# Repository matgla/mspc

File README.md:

# MSPC

Hardware for MSPC: a small modular computer built from a mainboard and extension cards that plug
into the MSPC bus. The mainboard runs [yasos](https://github.com/matgla/yasos.zig).

## Versions and branches

| branch | contents |
|---|---|
| `main` | the current hardware: the v2 boards (same as `mspc_v2`) |
| `mspc_v1` | the first generation, kept for reference |
| `mspc_v2` | the v2 boards as built |
| `mspc_v3` | the next revision (v3, not compatible with v2 cards), work in progress; `main` moves there when it is done and that point is tagged `mspcv3` |

## Repository layout

Every board is a KiCad project with its fabrication outputs next to it in `outputs/`.

| directory | board |
|---|---|
| `mainboard/` | Mainboard (project in `mainboard/mainboard/`). RP2350B (80-QFN), QSPI flash and PSRAM, microSD, HS8836A USB hub, TLV320DAC3203 audio DAC, 12 V input with BD9D321EFJ bucks, three MSPC bus sockets (2×10 and 2×15, 1.27 mm). 4 copper layers. |
| `gpu_vga_extension/` | VGA card: RP2350A (60-QFN), 2× W25Q32JV flash, AP2112K 3.3 V regulator, resistor-ladder RGB DAC and DB15 connector. 24 × 50 mm, 4 layers. |
| `gpu_dvi_card/` | DVI card: same core as the VGA card, with an HDMI-type receptacle carrying DVI. 24 × 50 mm, 4 layers. |
| `fpga_extension/` | FPGA card (project in `fpga_extension/fpga_extension/`): Lattice ECP5 LFE5UM-85F, W958D8NBYA HyperRAM, QSPI configuration flash, microSD, and an on-board RP2040 USB-C JTAG programmer. 47.5 × 50 mm, 6 layers. |
| `bus_adapter_20pin/` | Passive breakout from the 2×10 1.27 mm bus socket to two 1×10 2.54 mm headers. |
| `bus_adapter_30pin/` | Passive breakout from the 2×15 1.27 mm bus socket to two 1×15 2.54 mm headers. |
| `simulation/` | 2022 SPICE sandbox: KiCad/ngspice schematics (audio filter, power switch) and PySpice scripts. Not a board. |
| `libs/` | KiCad libraries shared by all boards (see below). |
| `docs/` | `mspc_v3_revision_plan.md` (v3 mainboard changes), `pcb_rules_jlcpcb.md` (mainboard stackup, JLCPCB order settings, fab export, design rules). |

## Working with the files

- The projects are in **KiCad 8** format. Newer KiCad versions upgrade them on the first save, and
  the result no longer opens in KiCad 8. Do such an upgrade as its own commit, with no design
  changes, so later diffs stay readable.
- Schematic PDFs (`outputs/schematic.pdf`) are tracked, so the schematics can be read without
  KiCad. Gerbers and drill files are not: plot them from the KiCad project when ordering a board.
  Per-machine files (backups, caches, `*.kicad_prl`, lock files, local history) are ignored too.

## Libraries

Every board uses the libraries in `libs/`. Each project's `sym-lib-table`, `fp-lib-table` and
`design-block-lib-table` point there through `${KIPRJMOD}`, so nothing has to be set up in KiCad.

| path | contents |
|---|---|
| `libs/symbols/` | symbol libraries, one per file; the nickname is the file name (`project_power`, `RP2040`, …) |
| `libs/footprints.pretty/` | footprints (nickname `footprints`) |
| `libs/RP2350_60QFN_minimal.pretty/`, `libs/RP2350_80QFN_minimal.pretty/` | RP2350 footprints and the small parts around them |
| `libs/3dmodels/` | STEP models; the footprints do not reference them yet |
| `libs/mspc.kicad_blocks/` | design blocks (KiCad 9+): circuits to reuse between boards, placed from the Design Blocks panel of the schematic editor. `TLV62569DRL_buck` is the FPGA card's 1.1 V buck. |

Add new parts to `libs/`, not to a project. A new symbol library file has to be added to the
`sym-lib-table` of every project.

## Known issues

- Some outputs are older than the boards they sit next to: the mainboard stencil (from v1), the
  GPU cards' schematic PDFs and stencils (from before the VGA/DVI split), and the FPGA card's
  schematic PDF. Regenerate them before the next order.
- The silkscreen of the 20-pin bus adapter reads "2x15" (copied from the 30-pin adapter).

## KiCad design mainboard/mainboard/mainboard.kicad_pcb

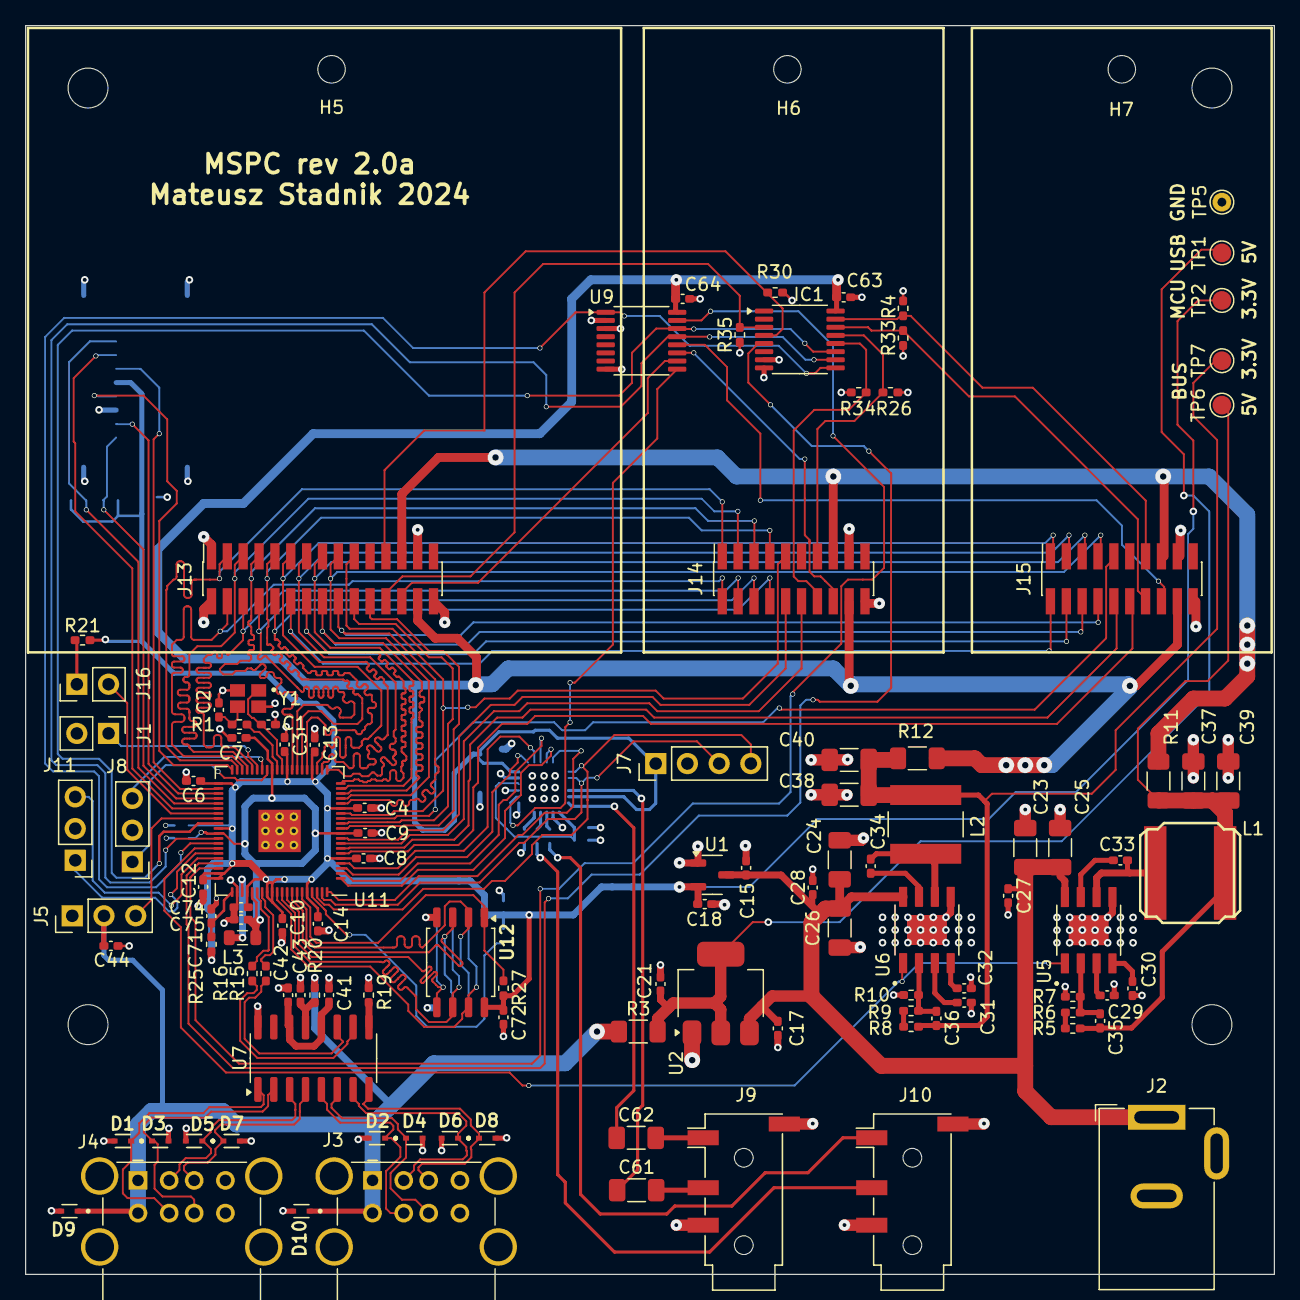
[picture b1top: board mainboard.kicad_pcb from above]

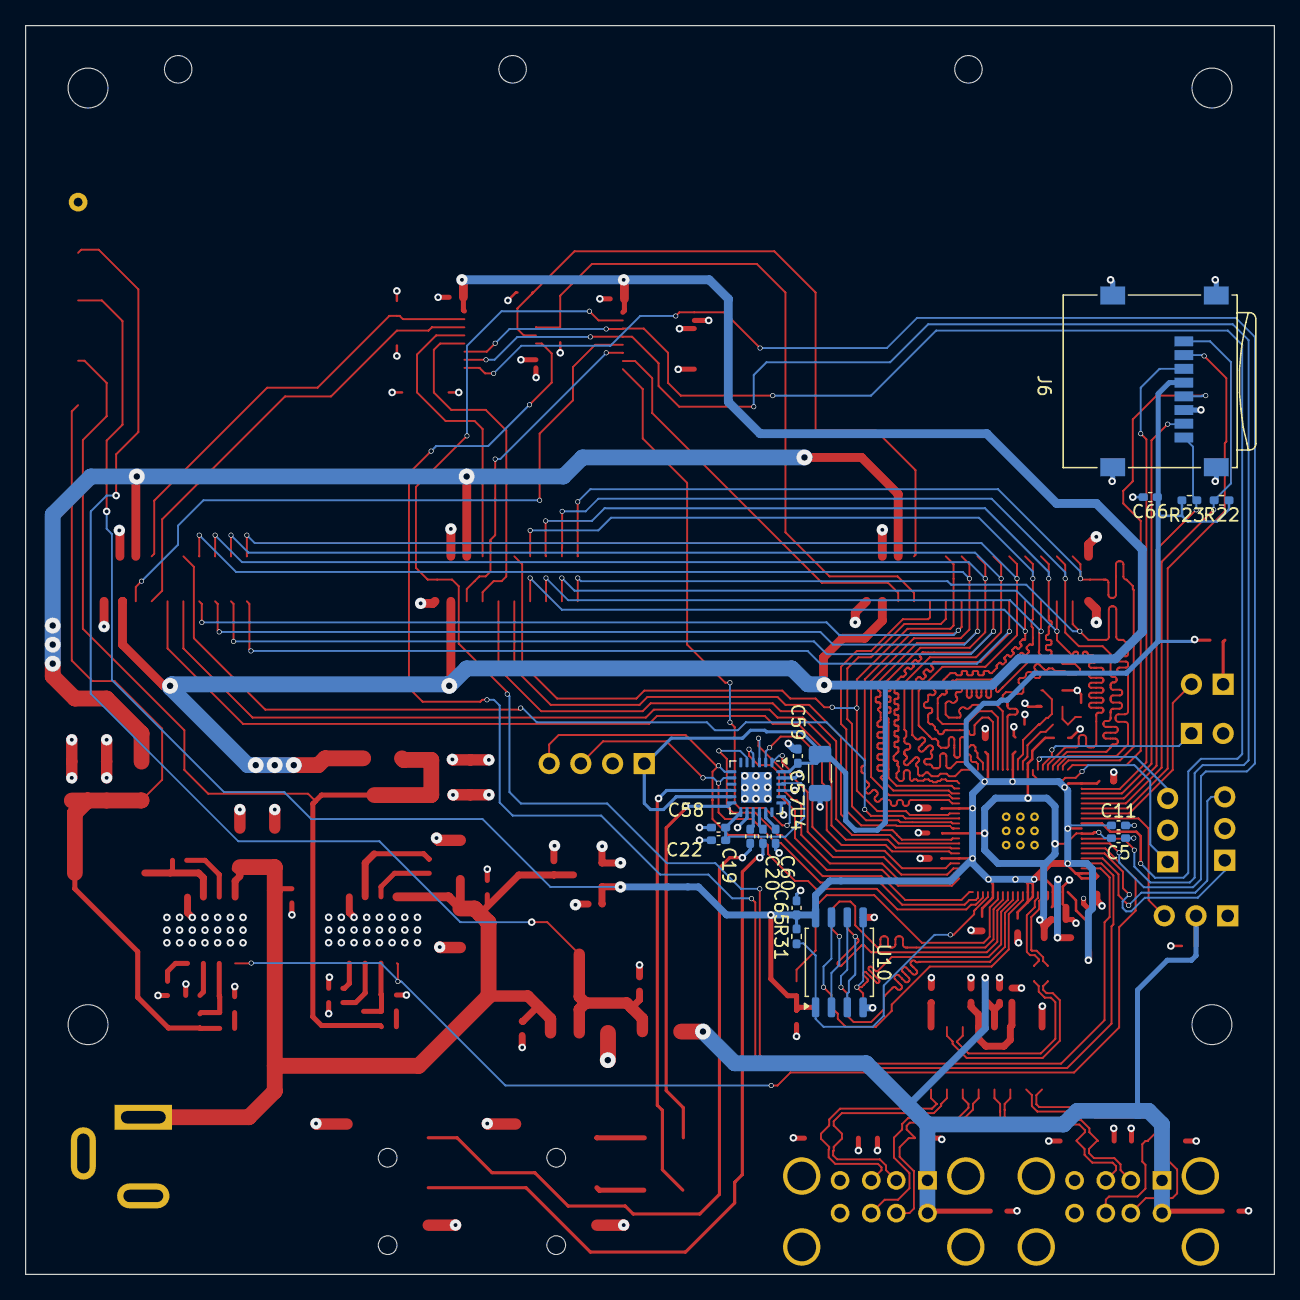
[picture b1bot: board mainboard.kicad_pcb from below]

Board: 4 copper layers, 100.0 x 100.0 mm, 135 parts (17 on the bottom side), 120 nets.

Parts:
C1, C2: 14p; C_0402_1005Metric_Pad0.74x0.62mm_HandSolder
C3, C4, C6, C7, C8, C9, C10, C11, C12, C13, C14, C19, C20, C27, C28, C33, C34, C42, C44, C58, C59, C63, C64, C65, C72: 100n; C_0402_1005Metric_Pad0.74x0.62mm_HandSolder
C5, C17, C41, C43, C71, C74, C75: 4.7u; C_0402_1005Metric_Pad0.74x0.62mm_HandSolder
C15, C22, C29, C31, C60: 1u; C_0402_1005Metric_Pad0.74x0.62mm_HandSolder
C18: 2.2u; C_0402_1005Metric_Pad0.74x0.62mm_HandSolder
C21: 10uF; C_0402_1005Metric_Pad0.74x0.62mm_HandSolder
C23, C24, C25, C26, C57: 10u; C_1206_3216Metric_Pad1.33x1.80mm_HandSolder
C30, C32: 3300p; C_0402_1005Metric_Pad0.74x0.62mm_HandSolder
C35, C36: 22p; C_0402_1005Metric_Pad0.74x0.62mm_HandSolder
C37, C38, C39, C40: 22u; C_1206_3216Metric_Pad1.33x1.80mm_HandSolder
C61, C62: 47u; C_1206_3216Metric_Pad1.33x1.80mm_HandSolder
C66: 10u; C_0402_1005Metric_Pad0.74x0.62mm_HandSolder
D1, D2, D3, D4, D5, D6, D7, D8, D9, D10: LESD5D5.0CT1G; TVS_LESD5D5.0CT1G
H1, H2, H3, H4: MountingHole; MountingHole_3.2mm_M3_DIN965
H5, H6, H7: MountingHole; MountingHole_2.2mm_M2_DIN965
IC1: SN74HCS151PWR; TSSOP-16_4.4x5mm_P0.65mm
J1, J16: Conn_01x02_Male; PinHeader_1x02_P2.54mm_Vertical
J2: Barrel_Jack_Switch; BarrelJack_GCT_DCJ200-10-A_Horizontal
J3, J4: USB_A_Wuerth_61400826021_Horizontal_Stacked
J5: Conn_01x03_Male; PinHeader_1x03_P2.54mm_Vertical
J6: Micro_SD_Card; microSD_HC_Wuerth_693072010801
J7: Conn_01x04_Female; PinHeader_1x04_P2.54mm_Vertical
J8, J11: Conn_01x03_Female; PinHeader_1x03_P2.54mm_Vertical
J9, J10: AudioJack4; Jack_3.5mm_PJ320D_Horizontal
J13: Connector A 16-bit; PinSocket_2x15_P1.27mm_Vertical_SMD
J14: Connector A 8-bit; PinSocket_2x10_P1.27mm_Vertical_SMD
J15: Connector B 8-bit; PinSocket_2x10_P1.27mm_Vertical_SMD
L1: 3.3u; NRS8030
L2: 2.2u; IND_NR6028T4R7M
L3: 3.3u; L_0805_2012Metric
R1, R21: 1k; R_0402_1005Metric_Pad0.72x0.64mm_HandSolder
R3, R11, R12: 0; R_1206_3216Metric_Pad1.30x1.75mm_HandSolder
R4, R22, R23, R26, R27, R30, R31, R33, R34, R35: 10k; R_0402_1005Metric_Pad0.72x0.64mm_HandSolder
R5: 120k; R_0402_1005Metric_Pad0.72x0.64mm_HandSolder
R6: 3.3k; R_0402_1005Metric_Pad0.72x0.64mm_HandSolder
R7, R10: 22k; R_0402_1005Metric_Pad0.72x0.64mm_HandSolder
R8: 68k; R_0402_1005Metric_Pad0.72x0.64mm_HandSolder
R9: 5.6k; R_0402_1005Metric_Pad0.72x0.64mm_HandSolder
R15, R16: 27.4R; R_0402_1005Metric_Pad0.72x0.64mm_HandSolder
R19: 100k; R_0402_1005Metric_Pad0.72x0.64mm_HandSolder
R20: 4.7; R_0402_1005Metric_Pad0.72x0.64mm_HandSolder
R25: 33; R_0402_1005Metric_Pad0.72x0.64mm_HandSolder
TP1, TP2, TP6, TP7: TestPoint; TestPoint_Pad_D1.5mm
TP5: TestPoint; TestPoint_THTPad_D1.5mm_Drill0.7mm
U1: AP2210; SOT-23-3
U2: LD1117S50TR_SOT223; SOT-223-3_TabPin2
U4: TLV320DAC3203IRGET; VQFN-24-1EP_4x4mm_P0.5mm_EP2.45x2.45mm
U5, U6: BD9D321EFJ; SOIC127P600X100-9N
U7: hs8836a; SOP-16_3.9x9.9mm_P1.27mm
U9: SN74LVC139APWR; TSSOP-16_4.4x5mm_P0.65mm
U10, U12: W25Q128JVS; SOIC-8_5.23x5.23mm_P1.27mm
U11: RP2350_80QFN; RP2350-QFN-80-1EP_10x10_P0.4mm_EP3.4x3.4mm_ThermalVias
Y1: ECS-120-8-36-CGN-TR; XTAL_ECS-120-8-36-CGN-TR

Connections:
+1V1_MCU: C5.1, C7.1, C9.1, C75.1, L3.1, U11.10 (DVDD), U11.32 (DVDD), U11.51 (DVDD), U11.65 (VREG_FB)
+3V3_BUS: C57.1, C59.1, C63.1, C64.1, IC1.16 (VCC), J7.1, J13.28, J14.18, J15.18, R12.1, U4.11 (LDOin), U4.24 (IOVDD), U9.16 (VCC)
+3V3_MCU: C3.1, C4.1, C6.1, C8.1, C10.1, C11.1, C12.1, C13.1, C14.1, C18.1, C65.1, C66.1, C72.1, C74.1, J6.4 (VDD), R21.2, R22.1, R23.1, R25.1, R27.2, R31.2, TP2.1, U1.2 (VOUT), U10.8 (VCC), U11.5 (IOVDD), U11.15 (IOVDD), U11.24 (IOVDD), U11.29 (IOVDD), U11.41 (IOVDD), U11.50 (IOVDD), U11.59 (ADC_AVDD), U11.60 (IOVDD), U11.64 (VREG_VIN), U11.68 (USB_OTP_VDD), U11.69 (QSPI_IOVDD), U11.76 (IOVDD), U12.8 (VCC)
+3V3_USB_HUB: C41.1, C42.1, U7.12 (DCP), U7.14 (V33)
+5V_BUS: J13.25, J14.15, J15.15, R11.1
+5V_VBUS: C44.1, D9.1, D10.1, J3.1 (VBUS1), J3.5 (VBUS2), J4.1 (VBUS1), J4.5 (VBUS2), J5.2, R3.1, R20.2
/RP2350 Core/Audio DAC/AUDIO.BCLK: U4.2 (BCLK), U11.4 (GPIO7)
/RP2350 Core/Audio DAC/AUDIO.DIN: U4.4 (DIN/MFP1), U11.1 (GPIO4)
/RP2350 Core/Audio DAC/AUDIO.DOUT: U4.5 (DOUT/MFP2), U11.80 (GPIO3)
/RP2350 Core/Audio DAC/AUDIO.MCLK: U4.1 (MCLK), U11.3 (GPIO6)
/RP2350 Core/Audio DAC/AUDIO.RESET#: U4.20 (RESET#), U9.9 (2Y3)
/RP2350 Core/Audio DAC/AUDIO.WCLK: U4.3 (WCLK), U11.2 (GPIO5)
/RP2350 Core/Audio DAC/AUDIO_OUT.L: C62.2, J9.T
/RP2350 Core/Audio DAC/AUDIO_OUT.R: C61.2, J9.R1
/RP2350 Core/Audio DAC/AUX_IN.L: C19.1, J10.T
/RP2350 Core/Audio DAC/AUX_IN.R: C20.1, J10.R1
/RP2350 Core/Audio DAC/I2C.SCL: J7.4, U4.7 (SCL/SS#), U11.78 (GPIO1)
/RP2350 Core/Audio DAC/I2C.SDA: J7.3, U4.8 (SDA/MOSI), U11.79 (GPIO2)
/RP2350 Core/BUS_DET_OUT: IC1.5 (Y), U11.57 (GPIO46_ADC6)
/RP2350 Core/BUS_RE#.IN: U9.15 (2G#), U11.58 (GPIO47_ADC7)
/RP2350 Core/MCU Connectors/BUS_CS#A0: J13.22, U11.11 (GPIO12)
/RP2350 Core/MCU Connectors/BUS_CS#A1: J13.20, U11.12 (GPIO13)
/RP2350 Core/MCU Connectors/BUS_CS#A2: J14.12, U11.8 (GPIO10)
/RP2350 Core/MCU Connectors/BUS_CS#A3: J14.10, U11.9 (GPIO11)
/RP2350 Core/MCU Connectors/BUS_CS#B0: J15.12, U11.6 (GPIO8)
/RP2350 Core/MCU Connectors/BUS_CS#B1: J15.10, U11.7 (GPIO9)
/RP2350 Core/MCU Connectors/BUS_DET.IN0: IC1.3 (D1), J13.24, R35.2
/RP2350 Core/MCU Connectors/BUS_DET.IN1: IC1.12 (D7), J14.14, R34.2
/RP2350 Core/MCU Connectors/BUS_DET.IN2: IC1.14 (D5), J15.14, R33.2
/RP2350 Core/MCU Connectors/BUS_INT.IN0: IC1.4 (D0), J13.23, R30.2
/RP2350 Core/MCU Connectors/BUS_INT.IN1: IC1.13 (D6), J14.13, R26.2
/RP2350 Core/MCU Connectors/BUS_INT.IN2: IC1.15 (D4), J15.13, R4.2
/RP2350 Core/MCU Connectors/BUS_NORTH.CLK0: J15.9, U11.13 (GPIO14)
/RP2350 Core/MCU Connectors/BUS_NORTH.CLK1: J13.19, J14.9, U11.14 (GPIO15)
/RP2350 Core/MCU Connectors/BUS_NORTH.D0: J13.18, J15.8, U11.16 (GPIO16)
/RP2350 Core/MCU Connectors/BUS_NORTH.D1: J13.17, J15.7, U11.17 (GPIO17)
/RP2350 Core/MCU Connectors/BUS_NORTH.D2: J13.16, J15.6, U11.18 (GPIO18)
/RP2350 Core/MCU Connectors/BUS_NORTH.D3: J13.15, J15.5, U11.19 (GPIO19)
/RP2350 Core/MCU Connectors/BUS_NORTH.D4: J13.14, J15.4, U11.20 (GPIO20)
/RP2350 Core/MCU Connectors/BUS_NORTH.D5: J13.13, J15.3, U11.21 (GPIO21)
/RP2350 Core/MCU Connectors/BUS_NORTH.D6: J13.12, J15.2, U11.22 (GPIO22)
/RP2350 Core/MCU Connectors/BUS_NORTH.D7: J13.11, J15.1, U11.23 (GPIO23)
/RP2350 Core/MCU Connectors/BUS_NORTH.D8: J13.10, J14.8, U11.25 (GPIO24)
/RP2350 Core/MCU Connectors/BUS_NORTH.D9: J13.9, J14.7, U11.26 (GPIO25)
/RP2350 Core/MCU Connectors/BUS_NORTH.D10: J13.8, J14.6, U11.27 (GPIO26)
/RP2350 Core/MCU Connectors/BUS_NORTH.D11: J13.7, J14.5, U11.28 (GPIO27)
/RP2350 Core/MCU Connectors/BUS_NORTH.D12: J13.6, J14.4, U11.36 (GPIO28)
/RP2350 Core/MCU Connectors/BUS_NORTH.D13: J13.5, J14.3, U11.37 (GPIO29)
/RP2350 Core/MCU Connectors/BUS_NORTH.D14: J13.4, J14.2, U11.38 (GPIO30)
/RP2350 Core/MCU Connectors/BUS_NORTH.D15: J13.3, J14.1, U11.39 (GPIO31)
/RP2350 Core/MCU Connectors/BUS_RE#.OUT0: J13.26, U9.10 (2Y2)
/RP2350 Core/MCU Connectors/BUS_RE#.OUT1: J14.16, U9.11 (2Y1)
/RP2350 Core/MCU Connectors/BUS_RE#.OUT2: J15.16, U9.12 (2Y0)
/RP2350 Core/MCU Connectors/DEBUG.SWCLK: J8.1, U11.33 (SWCLK)
/RP2350 Core/MCU Connectors/DEBUG.SWD: J8.3, U11.34 (SWD)
/RP2350 Core/MCU Connectors/UART.RX: J11.3, U11.56 (GPIO45_ADC5)
/RP2350 Core/MCU Connectors/UART.TX: J11.1, U11.55 (GPIO44_ADC4)
/RP2350 Core/MCU flash/QSPI.CSN0: R27.1, U11.75 (QSPI_SS), U12.1 (~CS)
/RP2350 Core/MCU flash/QSPI.CSN1: R31.1, U10.1 (~CS), U11.77 (GPIO0)
/RP2350 Core/MCU flash/QSPI.SCLK: U10.6 (CLK), U11.71 (QSPI_SCLK), U12.6 (CLK)
/RP2350 Core/MCU flash/QSPI.SD0: U10.5 (DI(IO0)), U11.72 (QSPI_SD0), U12.5 (DI(IO0))
/RP2350 Core/MCU flash/QSPI.SD1: U10.2 (DO(IO1)), U11.74 (QSPI_SD1), U12.2 (DO(IO1))
/RP2350 Core/MCU flash/QSPI.SD2: U10.3 (IO2), U11.73 (QSPI_SD2), U12.3 (IO2)
/RP2350 Core/MCU flash/QSPI.SD3: U10.7 (IO3), U11.70 (QSPI_SD3), U12.7 (IO3)
/RP2350 Core/MCU_RESET#: J1.1, U11.35 (RUN)
/RP2350 Core/Main bus control/BUS.CONTROL0: IC1.11 (A), U9.14 (2A), U11.49 (GPIO40_ADC0)
/RP2350 Core/Main bus control/BUS.CONTROL1: IC1.10 (B), U9.13 (2B), U11.52 (GPIO41_ADC1)
/RP2350 Core/Main bus control/BUS.CONTROL2: IC1.9 (C), U9.1 (1G#), U11.53 (GPIO42_ADC2)
/RP2350 Core/OSC_IN: C1.1, U11.30 (XIN), Y1.1 (IN/OUT)
/RP2350 Core/OSC_OUT: R1.2, U11.31 (XOUT)
/RP2350 Core/POWER_BUTTON: J16.2, U11.47 (GPIO38)
/RP2350 Core/POWER_LED_DATA: J5.3, U11.48 (GPIO39)
/RP2350 Core/SD Card/SDIO.CLK: J6.5 (CLK), U11.40 (GPIO32)
/RP2350 Core/SD Card/SDIO.CMD: J6.3 (CMD), U11.42 (GPIO33)
/RP2350 Core/SD Card/SDIO.D0: J6.7 (DAT0), U11.43 (GPIO34)
/RP2350 Core/SD Card/SDIO.D1: J6.8 (DAT1), R23.2, U11.44 (GPIO35)
/RP2350 Core/SD Card/SDIO.D2: J6.1 (DAT2), R22.2, U11.45 (GPIO36)
/RP2350 Core/SD Card/SDIO.D3: J6.2 (DAT3/CD), U11.46 (GPIO37)
/RP2350 Core/USB Hub/D1+: D8.1, J3.3 (D1+), U7.8 (DP1)
/RP2350 Core/USB Hub/D1-: D6.1, J3.2 (D1-), U7.7 (DM1)
/RP2350 Core/USB Hub/D2+: D4.1, J3.7 (D2+), U7.6 (DP2)
/RP2350 Core/USB Hub/D2-: D2.1, J3.6 (D2-), U7.5 (DM2)
/RP2350 Core/USB Hub/D3+: D7.1, J4.3 (D1+), U7.4 (DP3)
/RP2350 Core/USB Hub/D3-: D5.1, J4.2 (D1-), U7.3 (DM3)
/RP2350 Core/USB Hub/D4+: D3.1, J4.7 (D2+), U7.2 (DP4)
/RP2350 Core/USB Hub/D4-: D1.1, J4.6 (D2-), U7.1 (DM4)
/RP2350 Core/USB Hub/USB.D+: R16.2, U7.10 (DM)
/RP2350 Core/USB Hub/USB.D-: R15.2, U7.11 (DP)
/RP2350 Core/USB_D+: R16.1, U11.66 (USB_DM)
/RP2350 Core/USB_D-: R15.1, U11.67 (USB_DP)
/RP2350 Core/VREG_AVDD: C71.1, R25.2, U11.61 (VREG_AVDD)
/RP2350 Core/VREG_LX: L3.2, U11.63 (VREG_LX)
/power_supply/POWER_ENABLE: U5.1 (EN), U6.1 (EN), U11.54 (GPIO43_ADC3)
GND: C1.2, C2.2, C3.2, C4.2, C5.2, C6.2, C7.2, C8.2, C9.2, C10.2, C11.2, C12.2, C13.2, C14.2, C15.2, C17.2, C18.2, C21.2, C22.2, C23.2, C24.2, C25.2, C26.2, C27.2, C28.2, C29.2, C30.2, C31.2, C32.2, C37.2, C38.2, C39.2, C40.2, C41.2, C42.2, C43.2, C44.2, C57.2, C58.2, C59.2, C60.2, C63.2, C64.2, C65.2, C66.2, C71.2, C72.2, C74.2, C75.2, D1.2, D2.2, D3.2, D4.2, D5.2, D6.2, D7.2, D8.2, D9.2, D10.2, IC1.7 (~G), IC1.8 (GND), J1.2, J2.2, J3.4 (GND1), J3.8 (GND2), J3.9 (Shield), J4.4 (GND1), J4.8 (GND2), J4.9 (Shield), J5.1, J6.6 (VSS), J6.9 (SHIELD), J7.2, J8.2, J9.R2, J9.S, J10.R2, J10.S, J11.2, J13.1, J13.2, J13.27, J13.30, J14.17, J14.20, J15.17, J15.20, R4.1, R7.2, R10.2, R19.1, R26.1, R30.1, R33.1, R34.1, R35.1, TP5.1, U1.1 (GND), U2.1 (GND), U4.14 (AVSS), U4.19 (SPI_SELECT), U4.21 (DVSS), U4.23 (IOVSS), U5.5 (GND), U5.9 (FIN), U6.5 (GND), U6.9 (FIN), U7.16 (GND), U9.2 (1A), U9.3 (1B), U9.8 (GND), U10.4 (GND), U11.62 (VREG_PGND), U11.81 (GND), U12.4 (GND), Y1.2 (GND), Y1.4 (GND)
unnamed: C35.1, C37.1, C39.1, L1.2, R5.1, R11.2, TP6.1
unnamed: C36.1, C38.1, C40.1, L2.2, R8.1, R12.2, TP7.1
unnamed: J16.1, R21.1
unnamed: R5.2, R6.1
unnamed: R8.2, R9.1
unnamed: C21.1, R3.2, TP1.1, U2.2 (VO)
unnamed: C22.1, C58.1, U4.13 (AVDD), U4.22 (DVDD)
unnamed: C62.1, U4.12 (HPL)
unnamed: C61.1, U4.10 (HPR)
unnamed: C19.2, U4.15 (INL)
unnamed: C20.2, U4.16 (INR)
unnamed: C60.1, U4.17 (REF)
unnamed: C33.1, U5.7 (BOOT)
unnamed: C35.2, R6.2, R7.1, U5.2 (FB)
unnamed: C30.1, U5.4 (SS)
unnamed: C33.2, L1.1, U5.6 (SW)
unnamed: C29.1, U5.3 (VREG)
unnamed: C34.1, U6.7 (BOOT)
unnamed: C36.2, R9.2, R10.1, U6.2 (FB)
unnamed: C32.1, U6.4 (SS)
unnamed: C34.2, L2.1, U6.6 (SW)
unnamed: C31.1, U6.3 (VREG)
unnamed: R19.2, U7.9 (REF)
unnamed: C43.1, R20.1, U7.13 (VCC)
unnamed: C2.1, R1.1, Y1.3 (OUT/IN)
VDC: C15.1, C17.1, C23.1, C24.1, C25.1, C26.1, C27.1, C28.1, J2.1, U1.3 (VIN), U2.3 (VI), U5.8 (VIN), U6.8 (VIN)

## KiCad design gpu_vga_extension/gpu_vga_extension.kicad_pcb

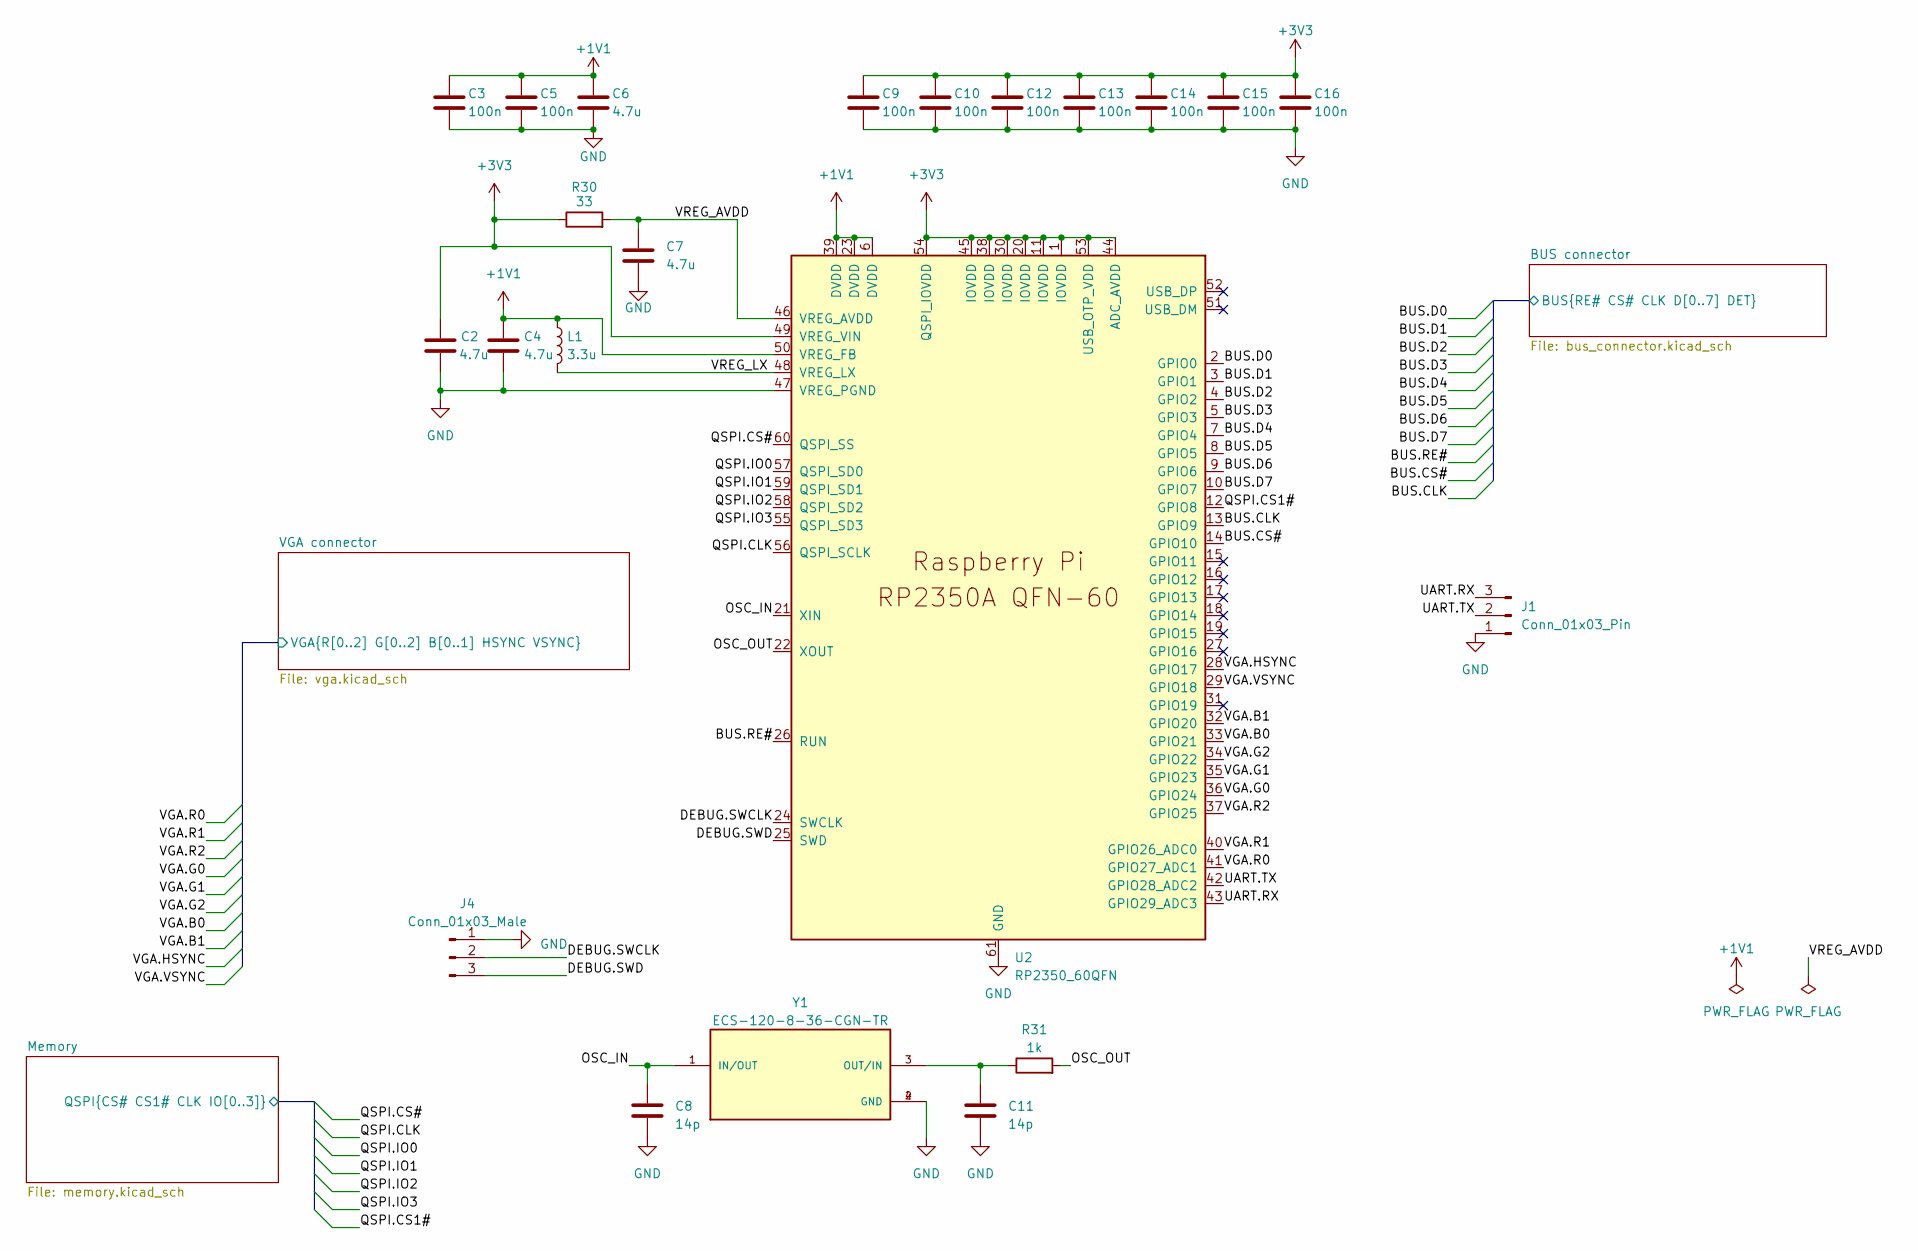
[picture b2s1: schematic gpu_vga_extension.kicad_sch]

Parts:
C2, C4, C6, C7: 4.7u; C_0402_1005Metric_Pad0.74x0.62mm_HandSolder
C3, C5, C9, C10, C12, C13, C14, C15, C16: 100n; C_0402_1005Metric_Pad0.74x0.62mm_HandSolder
C8, C11: 14p; C_0402_1005Metric_Pad0.74x0.62mm_HandSolder
J1: Conn_01x03_Pin; PinHeader_1x03_P2.54mm_Vertical
J4: Conn_01x03_Male; PinHeader_1x03_P2.54mm_Vertical
L1: 3.3u; L_0805_2012Metric_Pad1.15x1.40mm_HandSolder
R30: 33; R_0402_1005Metric_Pad0.72x0.64mm_HandSolder
R31: 1k; R_0402_1005Metric_Pad0.72x0.64mm_HandSolder
U2: RP2350_60QFN; RP2350-QFN-60-1EP_7x7_P0.4mm_EP3.4x3.4mm_ThermalVias
Y1: ECS-120-8-36-CGN-TR; XTAL_ECS-120-8-36-CGN-TR; PARTREV 2017

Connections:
+1V1: C3.1, C4.1, C5.1, C6.1, L1.1, U2.6 (DVDD), U2.23 (DVDD), U2.39 (DVDD), U2.50 (VREG_FB)
+3V3: C2.1, C9.1, C10.1, C12.1, C13.1, C14.1, C15.1, C16.1, R30.1, U2.1 (IOVDD), U2.11 (IOVDD), U2.20 (IOVDD), U2.30 (IOVDD), U2.38 (IOVDD), U2.44 (ADC_AVDD), U2.45 (IOVDD), U2.49 (VREG_VIN), U2.53 (USB_OTP_VDD), U2.54 (QSPI_IOVDD); also elsewhere on the board
/BUS connector/BUS.CLK: U2.13 (GPIO9); also elsewhere on the board
/BUS connector/BUS.CS#: U2.14 (GPIO10); also elsewhere on the board
/BUS connector/BUS.D0: U2.2 (GPIO0); also elsewhere on the board
/BUS connector/BUS.D1: U2.3 (GPIO1); also elsewhere on the board
/BUS connector/BUS.D2: U2.4 (GPIO2); also elsewhere on the board
/BUS connector/BUS.D3: U2.5 (GPIO3); also elsewhere on the board
/BUS connector/BUS.D4: U2.7 (GPIO4); also elsewhere on the board
/BUS connector/BUS.D5: U2.8 (GPIO5); also elsewhere on the board
/BUS connector/BUS.D6: U2.9 (GPIO6); also elsewhere on the board
/BUS connector/BUS.D7: U2.10 (GPIO7); also elsewhere on the board
/BUS connector/BUS.RE#: U2.26 (RUN); also elsewhere on the board
/DEBUG.SWCLK: J4.2, U2.24 (SWCLK)
/DEBUG.SWD: J4.3, U2.25 (SWD)
/Memory/QSPI.CLK: U2.56 (QSPI_SCLK); also elsewhere on the board
/Memory/QSPI.CS1#: U2.12 (GPIO8); also elsewhere on the board
/Memory/QSPI.CS#: U2.60 (QSPI_SS); also elsewhere on the board
/Memory/QSPI.IO0: U2.57 (QSPI_SD0); also elsewhere on the board
/Memory/QSPI.IO1: U2.59 (QSPI_SD1); also elsewhere on the board
/Memory/QSPI.IO2: U2.58 (QSPI_SD2); also elsewhere on the board
/Memory/QSPI.IO3: U2.55 (QSPI_SD3); also elsewhere on the board
/OSC_IN: C8.1, U2.21 (XIN), Y1.1 (IN/OUT)
/OSC_OUT: R31.2, U2.22 (XOUT)
/UART.RX: J1.3, U2.43 (GPIO29_ADC3)
/UART.TX: J1.2, U2.42 (GPIO28_ADC2)
/VGA connector/VGA.B0: U2.33 (GPIO21); also elsewhere on the board
/VGA connector/VGA.B1: U2.32 (GPIO20); also elsewhere on the board
/VGA connector/VGA.G0: U2.36 (GPIO24); also elsewhere on the board
/VGA connector/VGA.G1: U2.35 (GPIO23); also elsewhere on the board
/VGA connector/VGA.G2: U2.34 (GPIO22); also elsewhere on the board
/VGA connector/VGA.HSYNC: U2.28 (GPIO17); also elsewhere on the board
/VGA connector/VGA.R0: U2.41 (GPIO27_ADC1); also elsewhere on the board
/VGA connector/VGA.R1: U2.40 (GPIO26_ADC0); also elsewhere on the board
/VGA connector/VGA.R2: U2.37 (GPIO25); also elsewhere on the board
/VGA connector/VGA.VSYNC: U2.29 (GPIO18); also elsewhere on the board
/VREG_AVDD: C7.1, R30.2, U2.46 (VREG_AVDD)
/VREG_LX: L1.2, U2.48 (VREG_LX)
GND: C2.2, C3.2, C4.2, C5.2, C6.2, C7.2, C8.2, C9.2, C10.2, C11.2, C12.2, C13.2, C14.2, C15.2, C16.2, J1.1, J4.1, U2.47 (VREG_PGND), U2.61 (GND), Y1.2 (GND), Y1.4 (GND); also elsewhere on the board
unnamed: C11.1, R31.1, Y1.3 (OUT/IN)

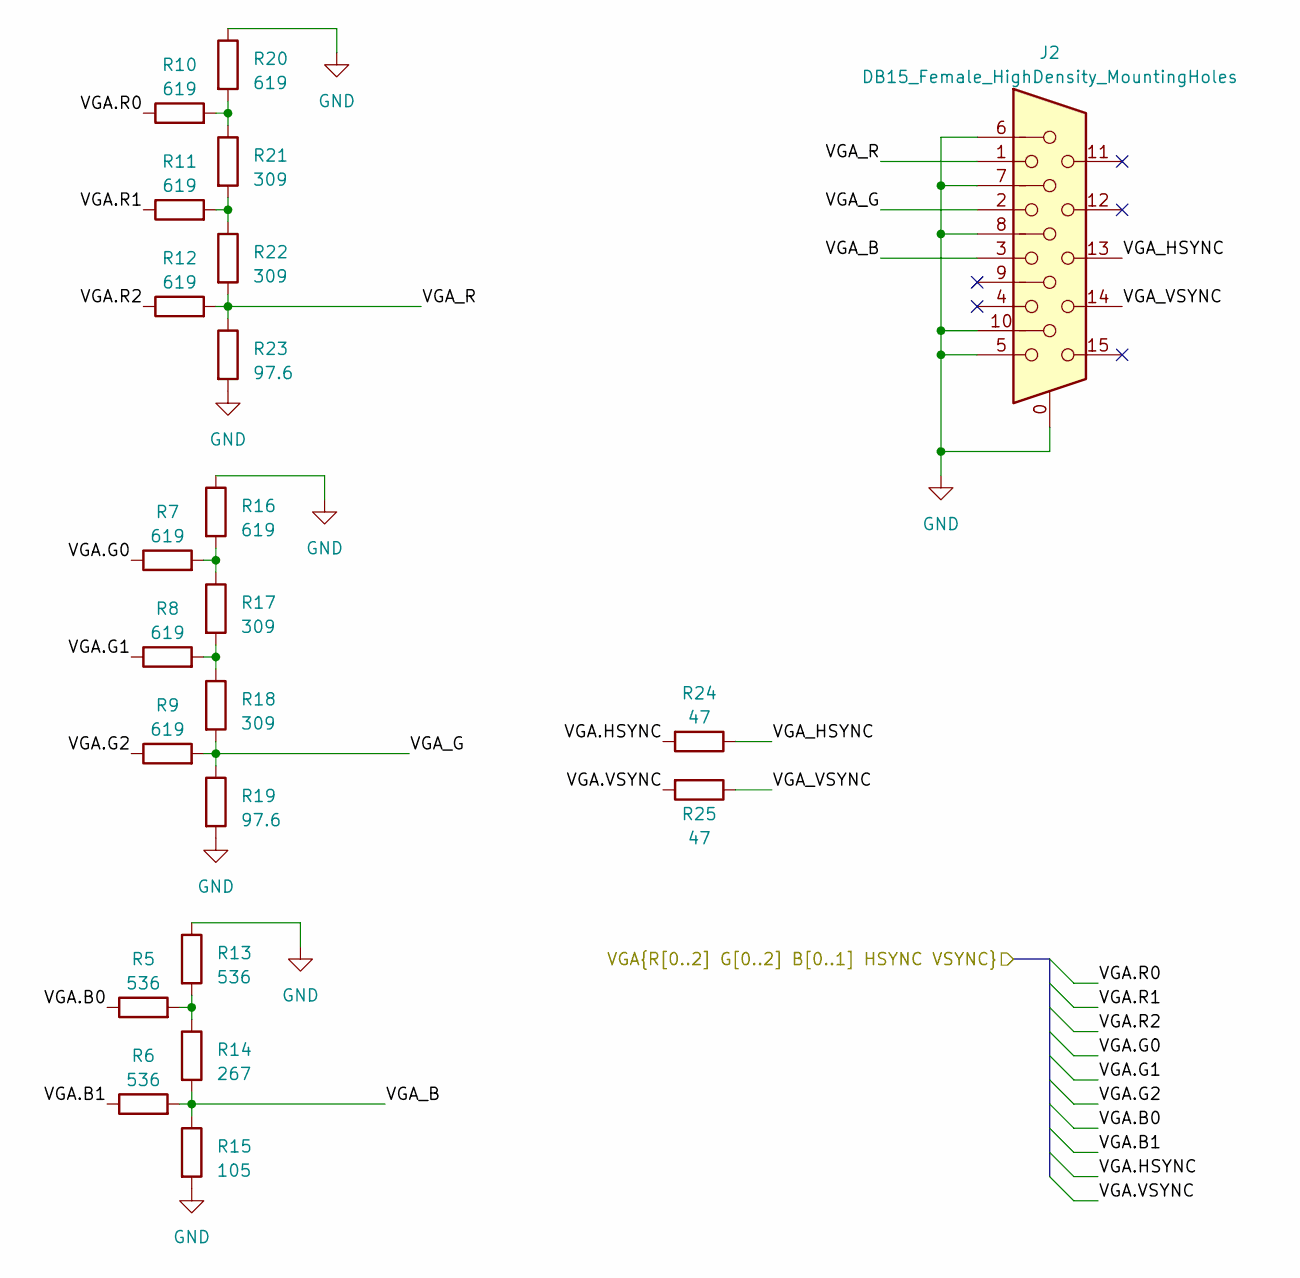
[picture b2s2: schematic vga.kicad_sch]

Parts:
J2: DB15_Female_HighDensity_MountingHoles; DSUB-15-HD_Female_Horizontal_P2.29x1.98mm_EdgePinOffset3.03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
R5, R6, R13: 536; R_0402_1005Metric_Pad0.72x0.64mm_HandSolder
R7, R8, R9, R10, R11, R12, R16, R20: 619; R_0402_1005Metric_Pad0.72x0.64mm_HandSolder
R14: 267; R_0402_1005Metric_Pad0.72x0.64mm_HandSolder
R15: 105; R_0402_1005Metric_Pad0.72x0.64mm_HandSolder
R17, R18, R21, R22: 309; R_0402_1005Metric_Pad0.72x0.64mm_HandSolder
R19, R23: 97.6; R_0402_1005Metric_Pad0.72x0.64mm_HandSolder
R24, R25: 47; R_0402_1005Metric_Pad0.72x0.64mm_HandSolder

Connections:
/VGA connector/VGA.B0: R5.1; also elsewhere on the board
/VGA connector/VGA.B1: R6.1; also elsewhere on the board
/VGA connector/VGA.G0: R7.1; also elsewhere on the board
/VGA connector/VGA.G1: R8.1; also elsewhere on the board
/VGA connector/VGA.G2: R9.1; also elsewhere on the board
/VGA connector/VGA.HSYNC: R24.2; also elsewhere on the board
/VGA connector/VGA.R0: R10.1; also elsewhere on the board
/VGA connector/VGA.R1: R11.1; also elsewhere on the board
/VGA connector/VGA.R2: R12.1; also elsewhere on the board
/VGA connector/VGA.VSYNC: R25.2; also elsewhere on the board
/VGA connector/VGA_B: J2.3, R6.2, R14.2, R15.1
/VGA connector/VGA_G: J2.2, R9.2, R18.2, R19.1
/VGA connector/VGA_HSYNC: J2.13, R24.1
/VGA connector/VGA_R: J2.1, R12.2, R22.2, R23.1
/VGA connector/VGA_VSYNC: J2.14, R25.1
GND: J2.0, J2.5, J2.6, J2.7, J2.8, J2.10, R13.1, R15.2, R16.1, R19.2, R20.1, R23.2; also elsewhere on the board
unnamed: R10.2, R20.2, R21.1
unnamed: R11.2, R21.2, R22.1
unnamed: R5.2, R13.2, R14.1
unnamed: R7.2, R16.2, R17.1
unnamed: R8.2, R17.2, R18.1

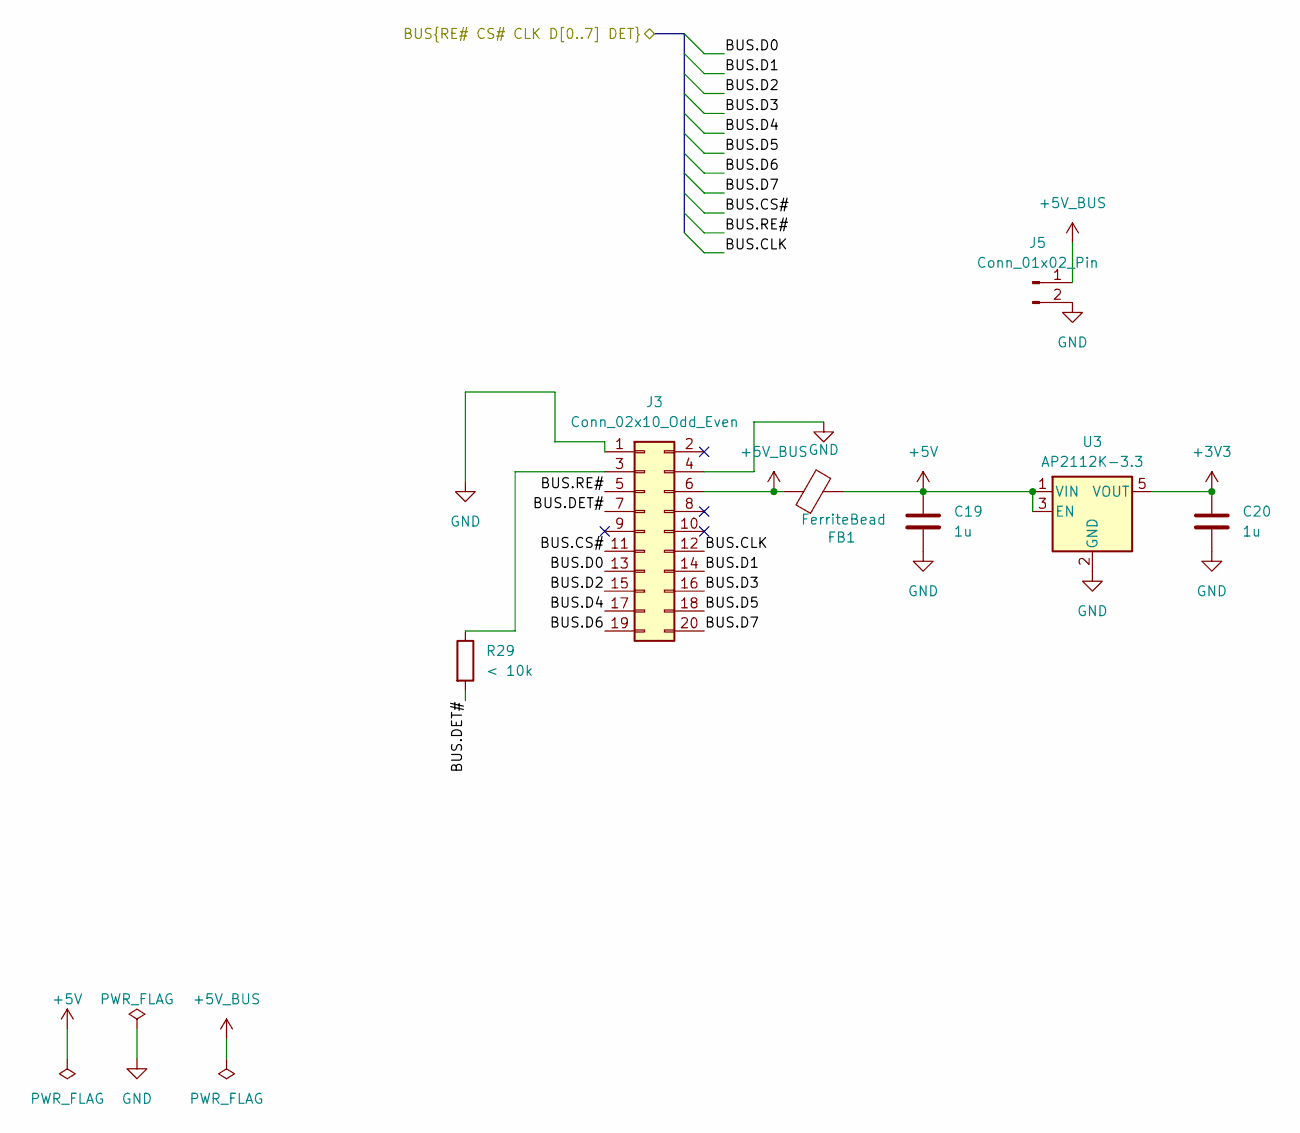
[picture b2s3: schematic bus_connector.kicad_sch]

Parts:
C19, C20: 1u; C_0402_1005Metric_Pad0.74x0.62mm_HandSolder
FB1: FerriteBead; L_0805_2012Metric_Pad1.05x1.20mm_HandSolder
J3: Conn_02x10_Odd_Even; PinHeader_2x10_P1.27mm_Vertical_SMD
J5: Conn_01x02_Pin; PinHeader_1x02_P2.54mm_Vertical
R29: < 10k; R_0402_1005Metric_Pad0.72x0.64mm_HandSolder
U3: AP2112K-3.3; SOT-23-5_HandSoldering

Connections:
+3V3: C20.1, U3.5 (VOUT); also elsewhere on the board
+5V: C19.1, FB1.2, U3.1 (VIN), U3.3 (EN)
+5V_BUS: FB1.1, J3.6, J5.1
/BUS connector/BUS.CLK: J3.12; also elsewhere on the board
/BUS connector/BUS.CS#: J3.11; also elsewhere on the board
/BUS connector/BUS.D0: J3.13; also elsewhere on the board
/BUS connector/BUS.D1: J3.14; also elsewhere on the board
/BUS connector/BUS.D2: J3.15; also elsewhere on the board
/BUS connector/BUS.D3: J3.16; also elsewhere on the board
/BUS connector/BUS.D4: J3.17; also elsewhere on the board
/BUS connector/BUS.D5: J3.18; also elsewhere on the board
/BUS connector/BUS.D6: J3.19; also elsewhere on the board
/BUS connector/BUS.D7: J3.20; also elsewhere on the board
/BUS connector/BUS.DET#: J3.7, R29.2
/BUS connector/BUS.RE#: J3.5; also elsewhere on the board
GND: C19.2, C20.2, J3.1, J3.4, J5.2, U3.2 (GND); also elsewhere on the board
unnamed: J3.3, R29.1

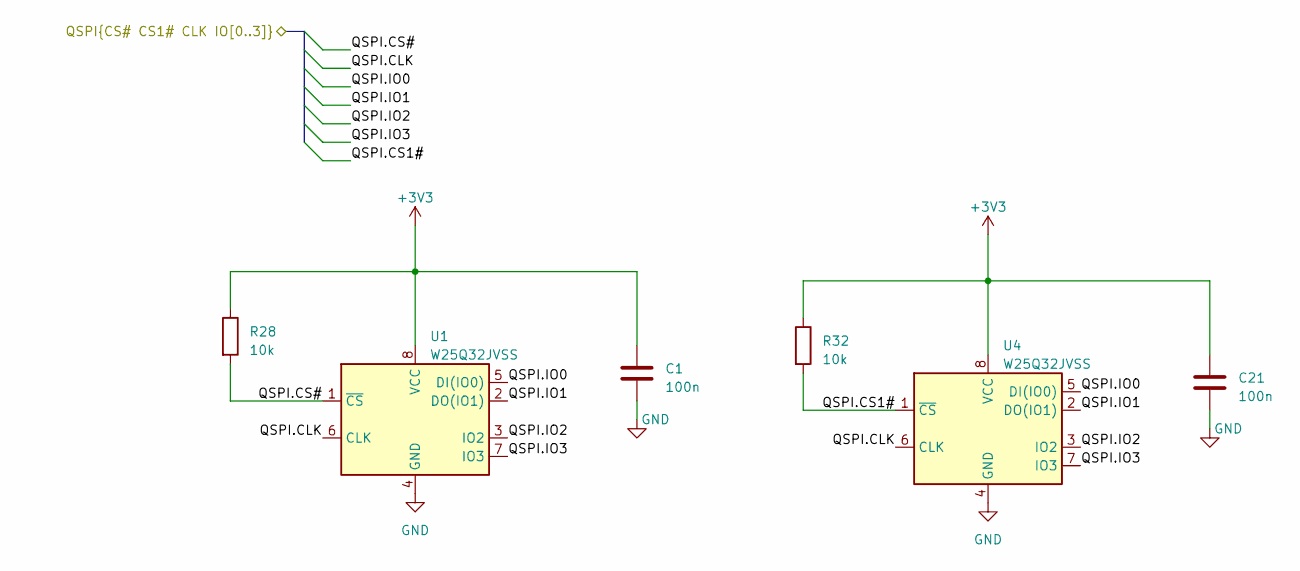
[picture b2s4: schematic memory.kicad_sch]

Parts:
C1, C21: 100n; C_0402_1005Metric_Pad0.74x0.62mm_HandSolder
R28, R32: 10k; R_0402_1005Metric_Pad0.72x0.64mm_HandSolder
U1, U4: W25Q32JVSS; SOIC-8_5.23x5.23mm_P1.27mm

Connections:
+3V3: C1.1, C21.1, R28.1, R32.1, U1.8 (VCC), U4.8 (VCC); also elsewhere on the board
/Memory/QSPI.CLK: U1.6 (CLK), U4.6 (CLK); also elsewhere on the board
/Memory/QSPI.CS1#: R32.2, U4.1 (~CS); also elsewhere on the board
/Memory/QSPI.CS#: R28.2, U1.1 (~CS); also elsewhere on the board
/Memory/QSPI.IO0: U1.5 (DI(IO0)), U4.5 (DI(IO0)); also elsewhere on the board
/Memory/QSPI.IO1: U1.2 (DO(IO1)), U4.2 (DO(IO1)); also elsewhere on the board
/Memory/QSPI.IO2: U1.3 (IO2), U4.3 (IO2); also elsewhere on the board
/Memory/QSPI.IO3: U1.7 (IO3), U4.7 (IO3); also elsewhere on the board
GND: C1.2, C21.2, U1.4 (GND), U4.4 (GND); also elsewhere on the board

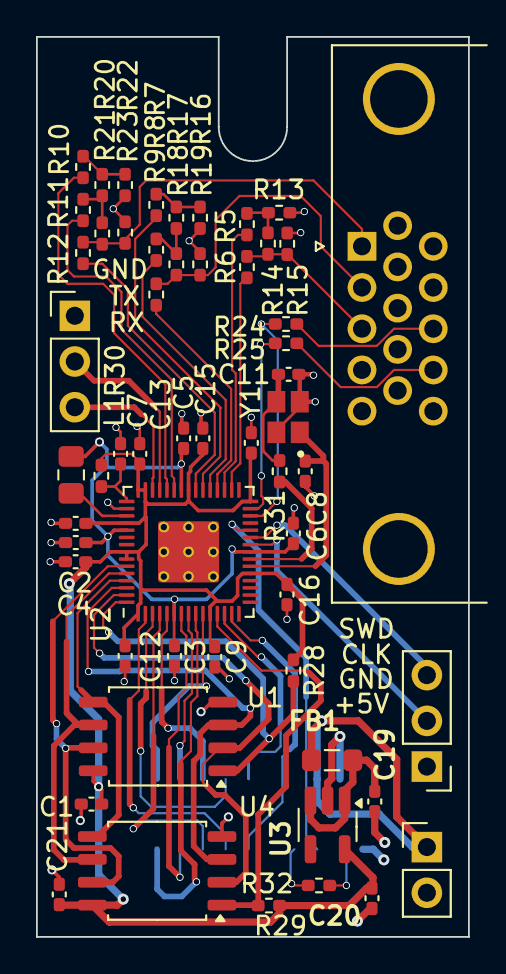
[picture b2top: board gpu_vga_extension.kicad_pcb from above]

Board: 4 copper layers, 24.0 x 50.0 mm, 57 parts (1 on the bottom side), 54 nets.
